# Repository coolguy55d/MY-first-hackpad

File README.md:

hi my name is Tharul and this is my first ever project attempt on creating a macropad ( aka hackpad ) . this project starts off as my first ever hardware project in my life . i picked this as this project seems interesting and easy to do . this project has many features such as :
a 5 key layout 
custom 3d printed case 
custom pcb 
and custom code 

to build a hackpad similar to my one you would require ; 
Seeed Studio XIAO RP2040 Microcontroller - 1 
MX-Compatible Mechanical switches - 5 
Custom Pcb - 1 ( according to the provided pcb cad files ) 
3d printed case with the top and bottom cover ( as provided according to the 3d files given ) 
M2 machine screws - 4 
1u mechanical Keycaps - 5 
usb-c data cable - 1 

all these items are fairly easy to find and are cheap in websites such as aliexpress except for the custom pcb which you might have to work with a local provider . 

the following file contains are given below;
`/macropad-design 2.2.f3d` - the full editable 3d file 
`/macropad_backcover.3mf` - the back casing 
`/macropad_top-cover_2.3mf` - the top covering 
`macropad.kicad_*` - the raw KiCad schematic and pcb files 

`CODE.py` - the firmware ( this code allows each switch to perform a various funtion , the funtions are ; copy and paste sumthing , mute and pause media . 

kicad pcb layouts and stuff for hackpad 

3d modelling in fusion for hackpad 

firmware for hackpad

the bill of materials ( BOM )

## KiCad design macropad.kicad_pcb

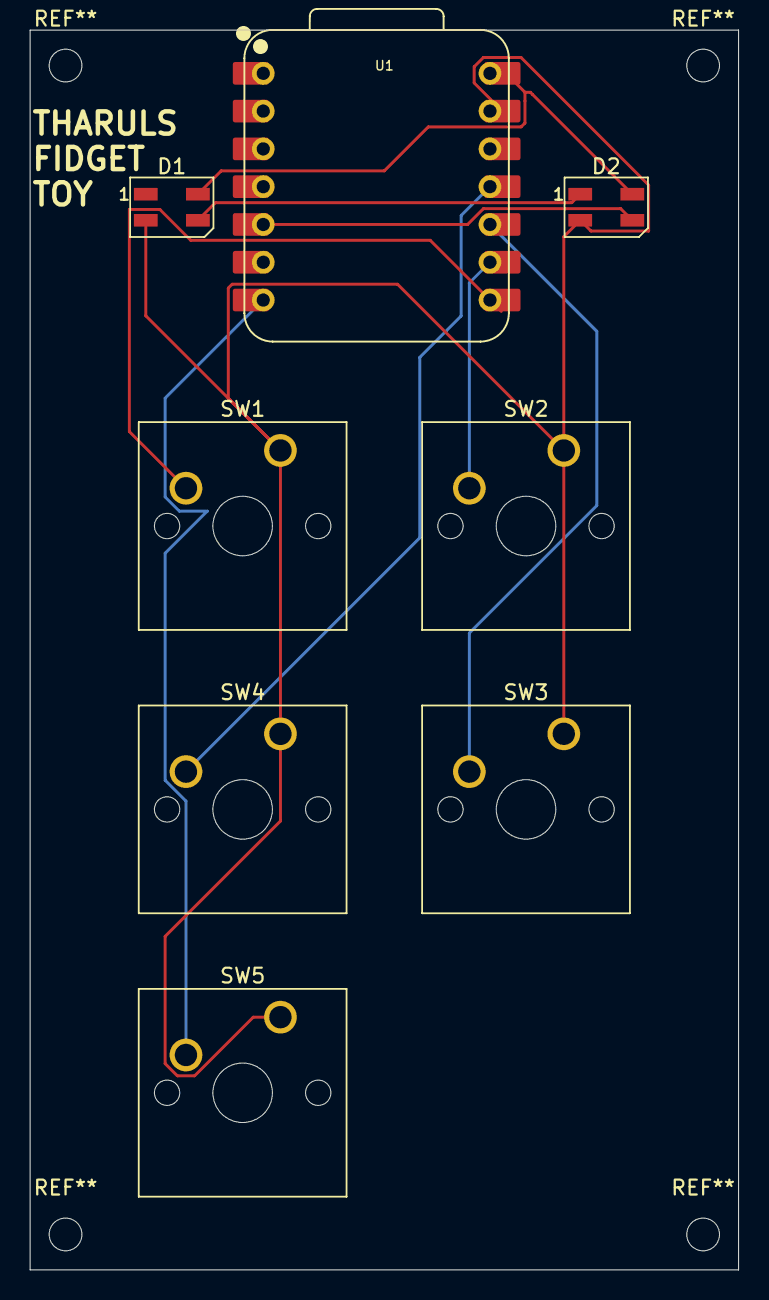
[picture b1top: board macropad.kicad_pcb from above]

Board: 2 copper layers, 47.6 x 83.3 mm, 8 parts (0 on the bottom side), 9 nets.

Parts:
D1, D2: SK6812MINI; LED_SK6812MINI_PLCC4_3.5x3.5mm_P1.75mm
SW1, SW2, SW3, SW4, SW5: SW_Push; SW_Cherry_MX_1.00u_PCB
U1: XIAO-RP2040-DIP

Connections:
+5V: D1.4 (VDD), D2.4 (VDD), U1.14 (VBUS)
GND: D1.2 (VSS), D2.2 (VSS), SW1.1, SW2.1, SW3.1, SW4.1, SW5.1, U1.13 (GND)
unnamed: D1.3 (DIN), D2.1 (DOUT)
unnamed: D2.3 (DIN), U1.5 (GPIO6/SDA)
unnamed: SW5.2, U1.7 (GPIO0/TX)
unnamed: SW1.2, U1.8 (GPIO1/RX)
unnamed: SW2.2, U1.9 (GPIO2/SCK)
unnamed: SW4.2, U1.11 (GPIO3/MOSI)
unnamed: SW3.2, U1.10 (GPIO4/MISO)

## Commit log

2026-05-21 Update README with project introduction
    Added a brief introduction about the hackpad project.
2026-05-21 README.md
    Corrected a typo in the README description.
2026-05-21 added the production files
    added my final production files into githubb
2026-05-21 Revise README with project details and features
    Updated README to provide detailed information about the custom macropad, including features, bill of materials, and repository contents.
2026-05-22 Add images to README for enhanced documentation
    Added images to the README for better visualization.
2026-05-22 Revise README with project details and BOM
    Updated README to include personal introduction, features, and detailed BOM for the custom macropad project.
2026-05-22 Fix terminology and update repository content descriptions
    Corrected terminology for the 3D printed case and updated descriptions for the repository contents.
2026-05-22 Remove next steps from README
    Removed the next steps section regarding firmware development.
2026-05-22 Rename top cover file in README
2026-05-22 Revise repository contents in README
    Updated repository contents section with new file names and formatting.
2026-06-09 Add BOM section to README with component details
    Added a BOM (Bill of Materials) section with details on components needed for the project, including links and costs.
2026-06-09 Remove bill of materials from README
    Removed bill of materials section with product details.
2026-06-15 Revise README for macropad project details
    Updated project description and features for clarity. Added detailed bill of materials and file contents.
2026-06-15 Update README with design files and firmware info
    Added details about design files and firmware functionality.
2026-06-15 Update image in README with a larger version
